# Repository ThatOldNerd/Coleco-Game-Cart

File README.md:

# Coleco-Game-Cart
This is a generic game cartridge for the Colecovision console

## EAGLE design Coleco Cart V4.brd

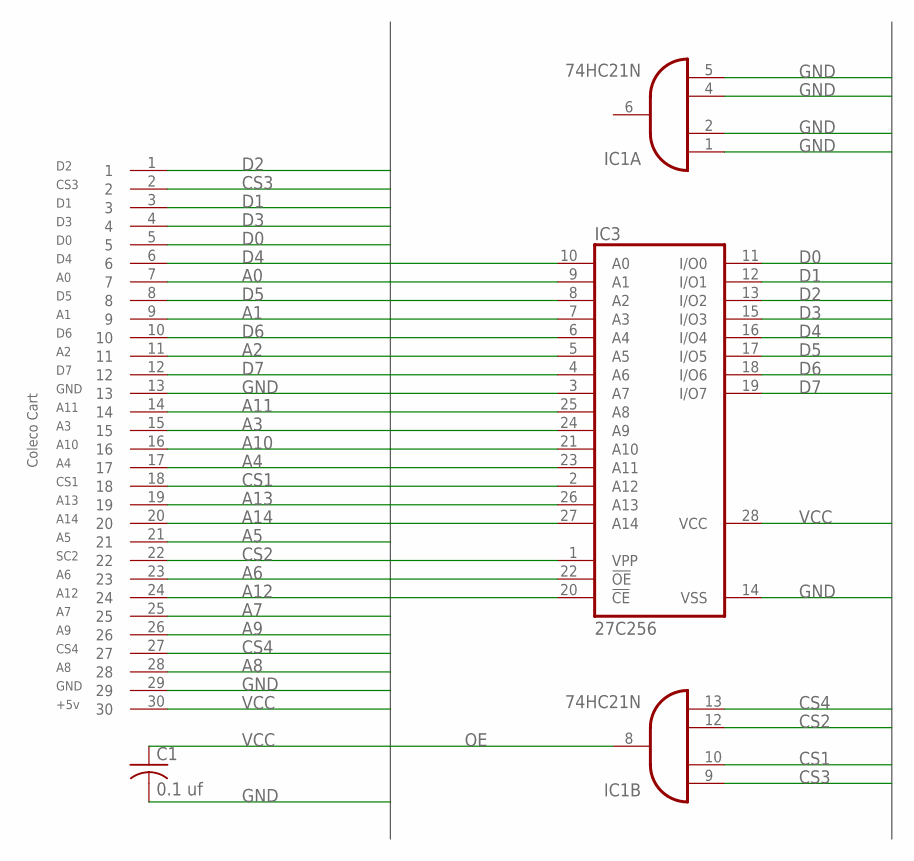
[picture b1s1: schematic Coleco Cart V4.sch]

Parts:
C1: 0.1 uf; C050-030X075
IC1: 74HC21N; DIL14
IC3: 27C256; DIL28-6
U$1: CART

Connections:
A0: IC3.10 (A0), U$1.7
A1: IC3.9 (A1), U$1.9
A2: IC3.8 (A2), U$1.11
A3: IC3.7 (A3), U$1.15
A4: IC3.6 (A4), U$1.17
A5: IC3.5 (A5), U$1.21
A6: IC3.4 (A6), U$1.23
A7: IC3.3 (A7), U$1.25
A8: IC3.25 (A8), U$1.28
A9: IC3.24 (A9), U$1.26
A10: IC3.21 (A10), U$1.16
A11: IC3.23 (A11), U$1.14
A12: IC3.2 (A12), U$1.24
A13: IC3.26 (A13), U$1.19
A14: IC3.27 (A14), U$1.20
CS1: IC1.10 (I1), U$1.18
CS2: IC1.12 (I2), U$1.22
CS3: IC1.9 (I0), U$1.2
CS4: IC1.13 (I3), U$1.27
D0: IC3.11 (I/O0), U$1.5
D1: IC3.12 (I/O1), U$1.3
D2: IC3.13 (I/O2), U$1.1
D3: IC3.15 (I/O3), U$1.4
D4: IC3.16 (I/O4), U$1.6
D5: IC3.17 (I/O5), U$1.8
D6: IC3.18 (I/O6), U$1.10
D7: IC3.19 (I/O7), U$1.12
GND: C1.2, IC1.1 (I0), IC1.2 (I1), IC1.4 (I2), IC1.5 (I3), IC1.7 (GND), IC3.14 (VSS), U$1.13, U$1.29
OE: IC1.8 (O), IC3.20 (!CE), IC3.22 (!OE)
VCC: C1.1, IC1.14 (VCC), IC3.1 (VPP), IC3.28 (VCC), U$1.30

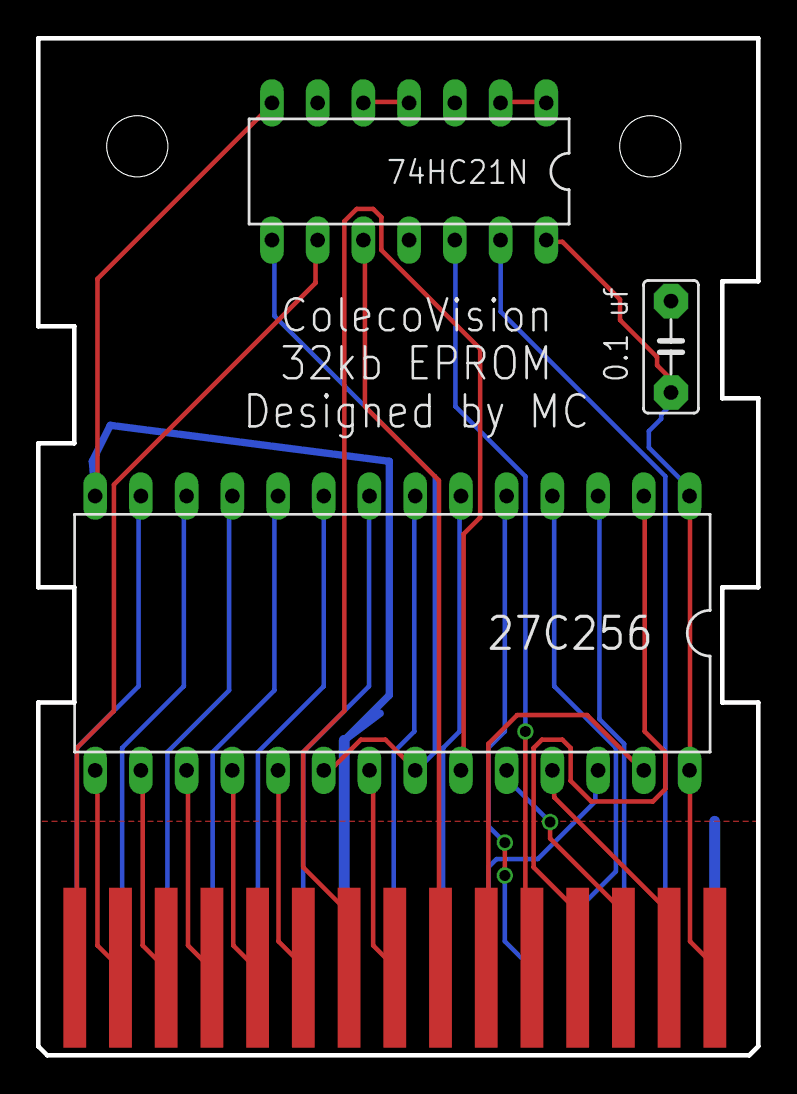
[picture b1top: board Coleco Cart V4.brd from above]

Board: 2 copper layers, 40.0 x 56.5 mm, 4 parts (0 on the bottom side), 30 nets.
